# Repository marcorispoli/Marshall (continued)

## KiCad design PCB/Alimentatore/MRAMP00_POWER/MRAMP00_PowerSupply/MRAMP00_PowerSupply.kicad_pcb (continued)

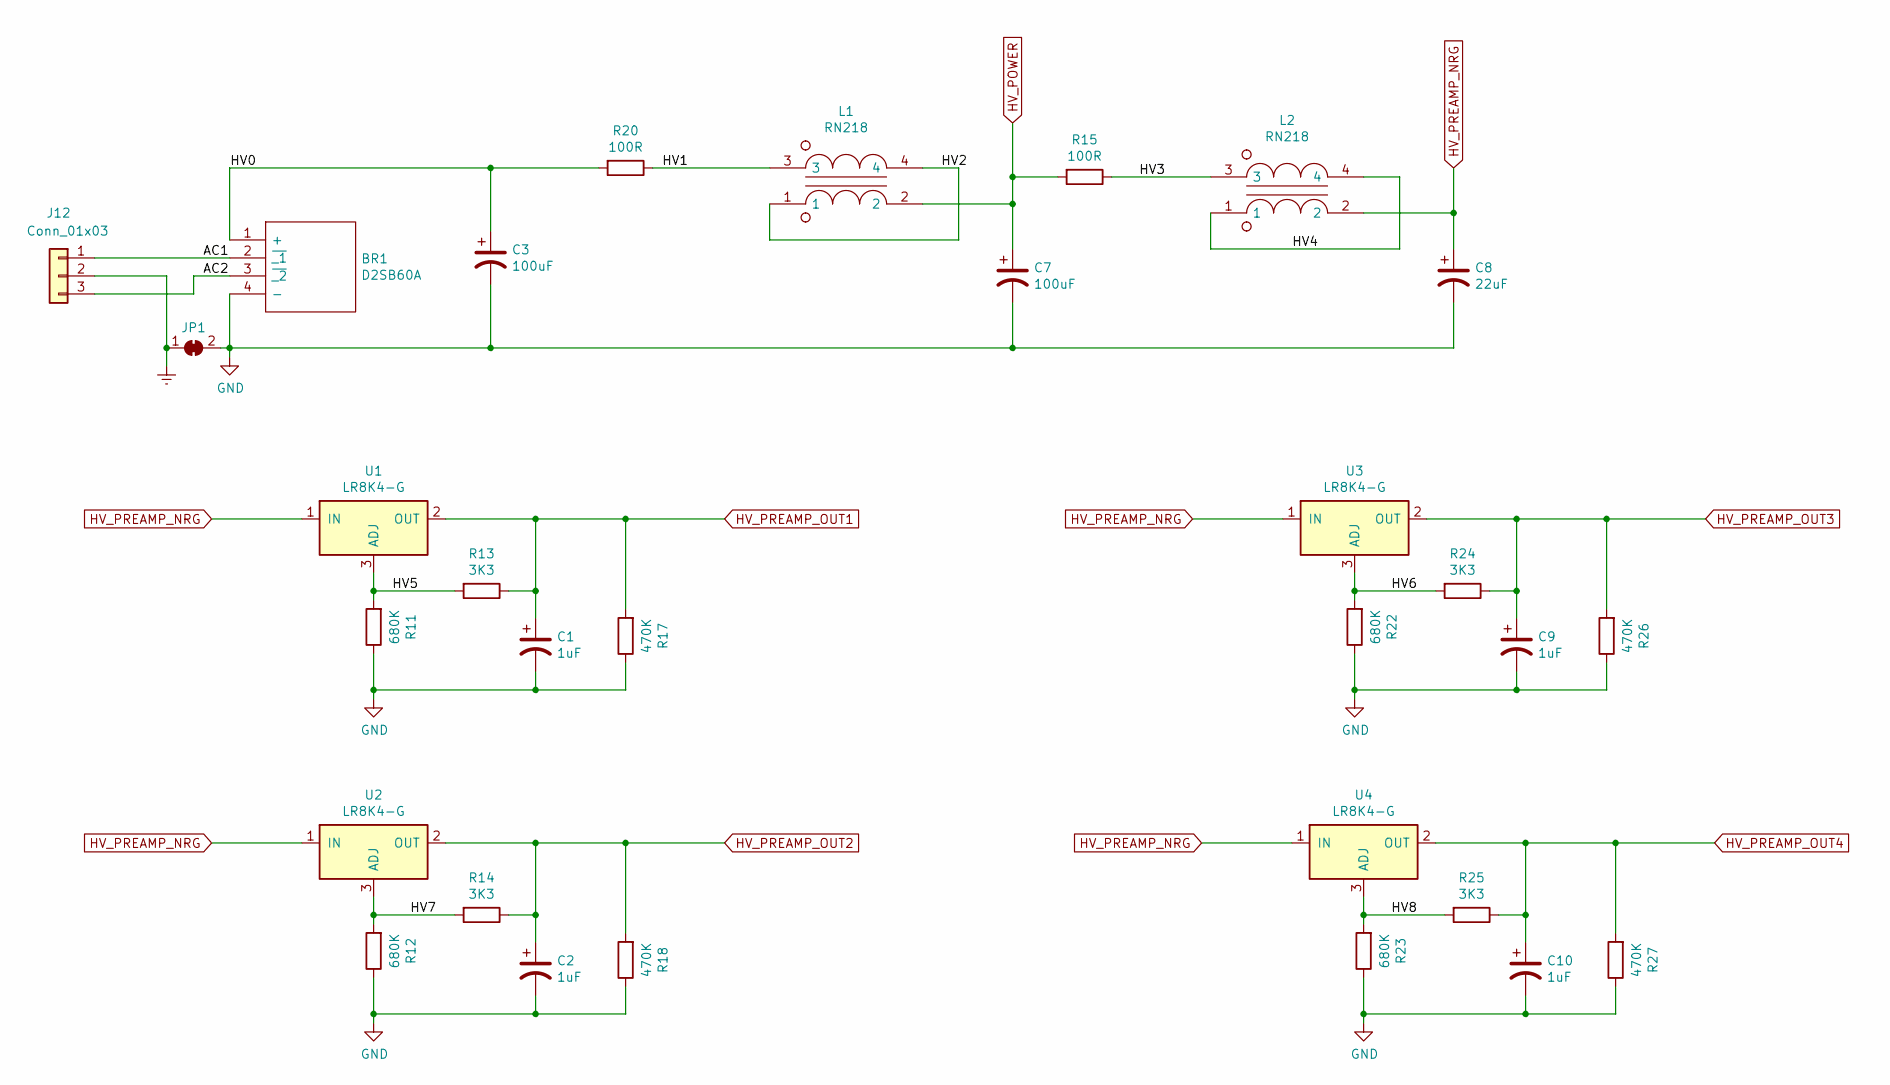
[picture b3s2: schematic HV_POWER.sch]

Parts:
BR1: D2SB60A; TO500P370X2000X1400-4P
C1, C2, C9, C10: 1uF; CP_Radial_D8.0mm_P3.50mm
C3, C7: 100uF; CP_Radial_D18.0mm_P7.50mm
C8: 22uF; CP_Radial_D12.5mm_P5.00mm
J12: Conn_01x03; PhoenixContact_GMSTBVA_2,5_3-G_1x03_P7.50mm_Vertical
JP1: SolderJumper_2_Bridged; SolderJumper-2_P1.3mm_Bridged_Pad1.0x1.5mm
L1, L2: RN218; Choke_Schaffner_RN218-04-12.5x18.0mm
R11, R12, R22, R23: 680K; R_2512_6332Metric_Pad1.40x3.35mm_HandSolder
R13, R14, R24, R25: 3K3; R_1206_3216Metric_Pad1.30x1.75mm_HandSolder
R15, R20: 100R; R_2512_6332Metric_Pad1.40x3.35mm_HandSolder
R17, R18, R26, R27: 470K; R_2512_6332Metric_Pad1.40x3.35mm_HandSolder
U1, U2, U3, U4: LR8K4-G; TO-252-2

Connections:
/HV_POWER/AC1: BR1.2 (~_1), J12.1
/HV_POWER/AC2: BR1.3 (~_2), J12.3
/HV_POWER/HV0: BR1.1 (+), C3.1, R20.2
/HV_POWER/HV1: L1.3, R20.1
/HV_POWER/HV2: L1.1, L1.4
/HV_POWER/HV3: L2.3, R15.1
/HV_POWER/HV4: L2.1, L2.4
/HV_POWER/HV5: R11.2, R13.2, U1.3 (ADJ)
/HV_POWER/HV6: R22.2, R24.2, U3.3 (ADJ)
/HV_POWER/HV7: R12.2, R14.2, U2.3 (ADJ)
/HV_POWER/HV8: R23.2, R25.2, U4.3 (ADJ)
Earth: J12.2, JP1.1 (A); also elsewhere on the board
GND: BR1.4 (-), C1.2, C2.2, C3.2, C7.2, C8.2, C9.2, C10.2, JP1.2 (B), R11.1, R12.1, R17.1, R18.1, R22.1, R23.1, R26.1, R27.1; also elsewhere on the board
HV_POWER: C7.1, L1.2, R15.2; also elsewhere on the board
HV_PREAMP_NRG: C8.1, L2.2, U1.1 (IN), U2.1 (IN), U3.1 (IN), U4.1 (IN)
HV_PREAMP_OUT1: C1.1, R13.1, R17.2, U1.2 (OUT); also elsewhere on the board
HV_PREAMP_OUT2: C2.1, R14.1, R18.2, U2.2 (OUT); also elsewhere on the board
HV_PREAMP_OUT3: C9.1, R24.1, R26.2, U3.2 (OUT); also elsewhere on the board
HV_PREAMP_OUT4: C10.1, R25.1, R27.2, U4.2 (OUT); also elsewhere on the board

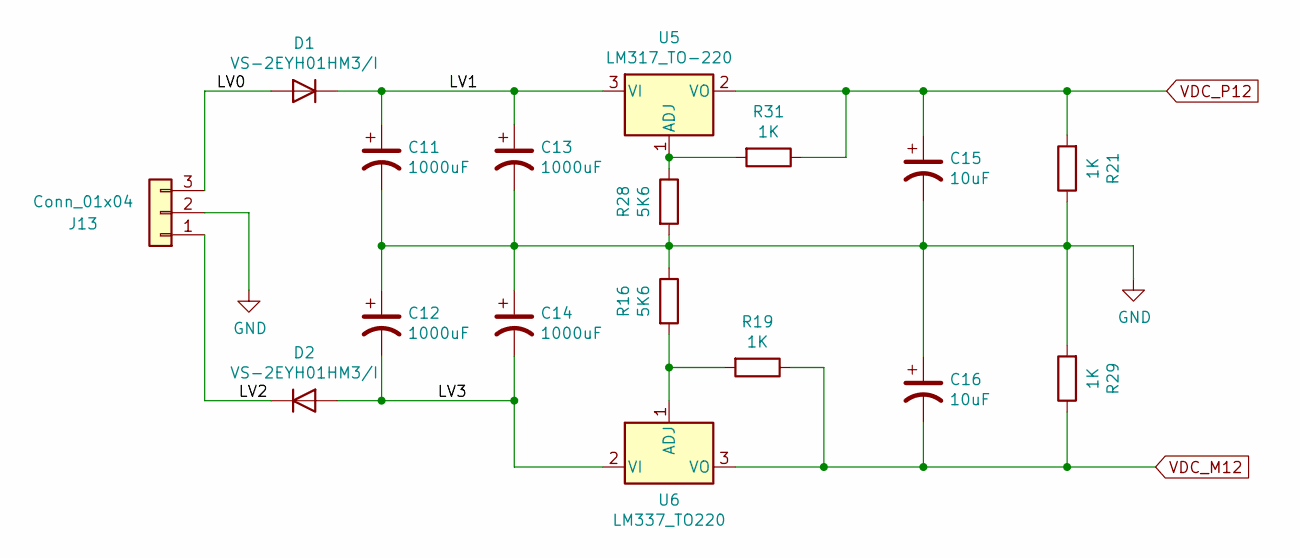
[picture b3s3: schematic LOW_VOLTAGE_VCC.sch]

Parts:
C11, C12, C13, C14: 1000uF; CP_Radial_D10.0mm_P5.00mm
C15, C16: 10uF; CP_Radial_D5.0mm_P2.00mm
D1, D2: VS-2EYH01HM3/I; D_SOD-128
J13: Conn_01x04; PhoenixContact_GMSTBVA_2,5_3-G_1x03_P7.50mm_Vertical
R16, R28: 5K6; R_1206_3216Metric_Pad1.30x1.75mm_HandSolder
R19, R21, R29, R31: 1K; R_1206_3216Metric_Pad1.30x1.75mm_HandSolder
U5: LM317_TO-220; TO-220-3_Horizontal_TabDown
U6: LM337_TO220; TO-220-3_Horizontal_TabDown

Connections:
/LOW_VOLTAGE_VCC/LV0: D1.2 (A), J13.3
/LOW_VOLTAGE_VCC/LV1: C11.1, C13.1, D1.1 (K), U5.3 (VI)
/LOW_VOLTAGE_VCC/LV2: D2.1 (K), J13.1
/LOW_VOLTAGE_VCC/LV3: C12.2, C14.2, D2.2 (A), U6.2 (VI)
GND: C11.2, C12.1, C13.2, C14.1, C15.2, C16.1, J13.2, R16.1, R21.1, R28.2, R29.2; also elsewhere on the board
unnamed: R16.2, R19.2, U6.1 (ADJ)
unnamed: R28.1, R31.2, U5.1 (ADJ)
VDC_M12: C16.2, R19.1, R29.1, U6.3 (VO); also elsewhere on the board
VDC_P12: C15.1, R21.2, R31.1, U5.2 (VO); also elsewhere on the board

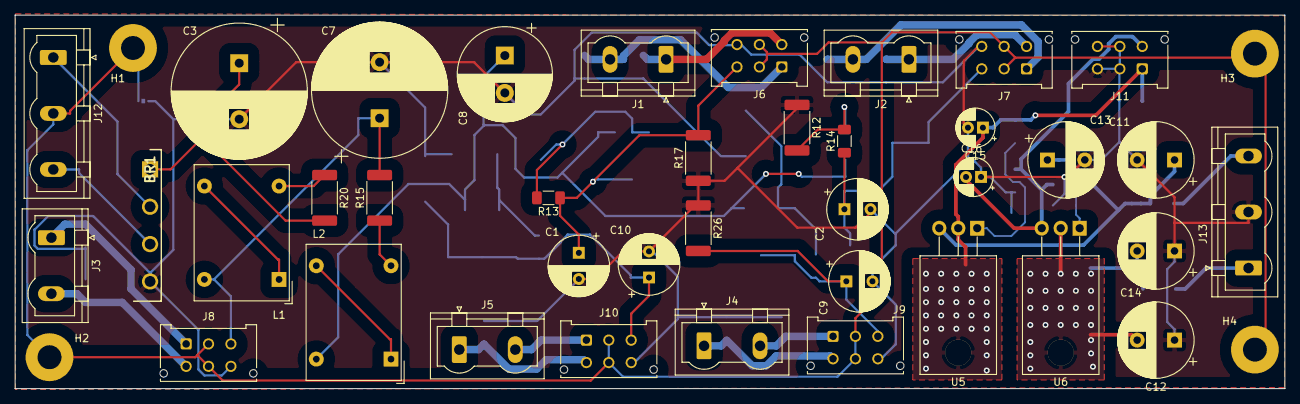
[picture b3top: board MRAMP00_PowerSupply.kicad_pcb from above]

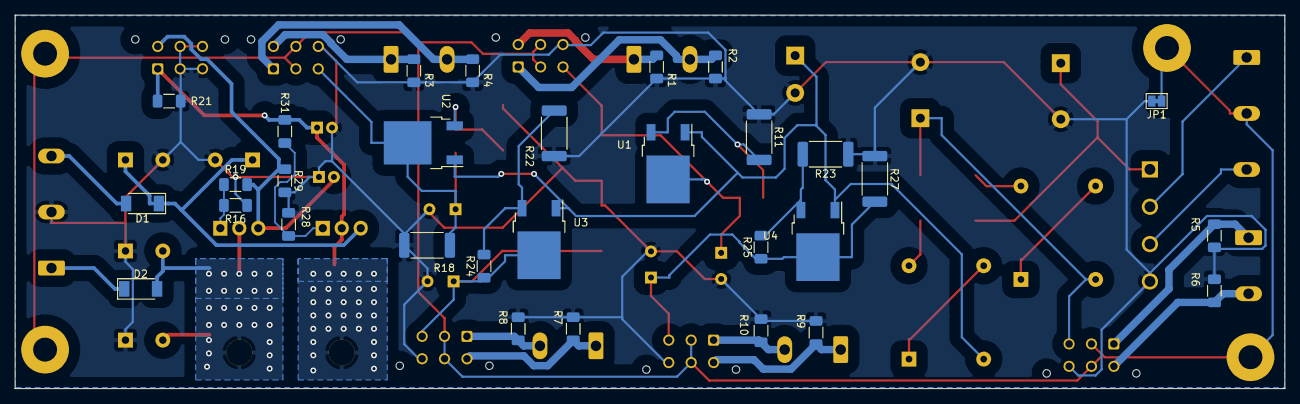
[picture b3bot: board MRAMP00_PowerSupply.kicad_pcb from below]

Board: 2 copper layers, 170.0 x 50.0 mm, 72 parts (30 on the bottom side), 37 nets.

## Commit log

2021-07-26 Doc vari
2021-07-29 Aggiornato progetto KiCad
2021-08-03 modificato booster
2021-08-04 jubilee pre-amp
2021-08-05 avanzamento pcb
2021-08-05 aggiunti steps
2021-08-26 sbrogliato pcb pre-ampli
2025-03-15 Ultima release
2025-03-15 Ultima release rimasterizzata per aumentare le distanze. Questa è stataprodotta da JLCPCB
